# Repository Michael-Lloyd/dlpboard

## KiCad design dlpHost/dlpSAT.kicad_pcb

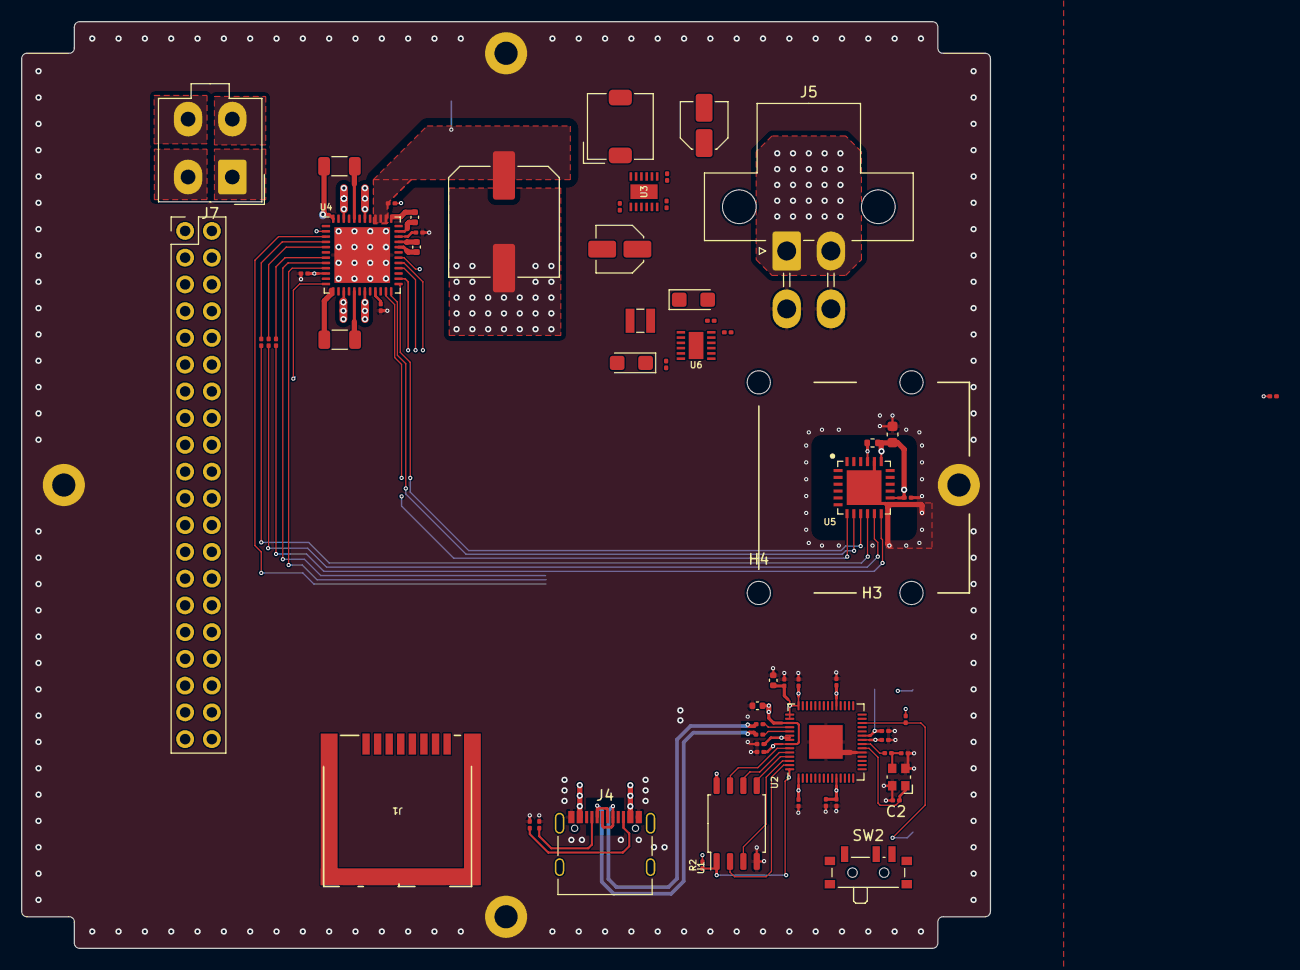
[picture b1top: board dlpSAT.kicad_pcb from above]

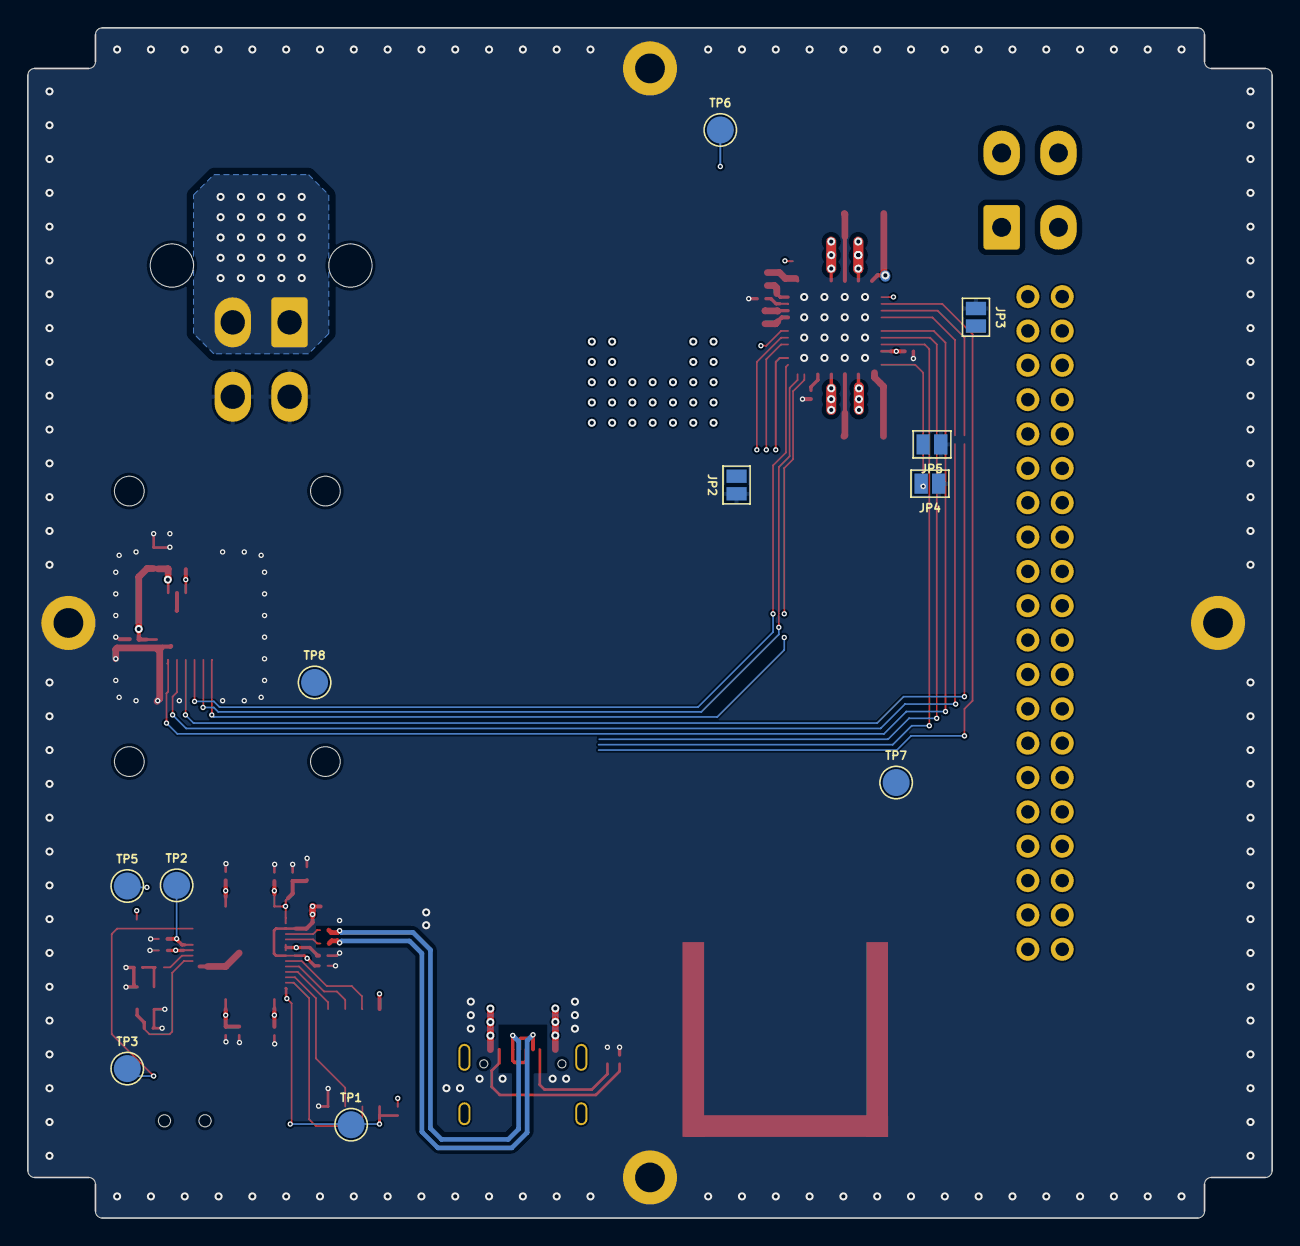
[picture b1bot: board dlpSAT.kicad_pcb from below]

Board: 4 copper layers, 92.0 x 88.0 mm, 77 parts (11 on the bottom side), 49 nets.

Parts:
BRD1: 100STD_BLUESAT; Rocket_Layout
C2, C3: C; C_0201_0603Metric
C4, C15: 1µF; C_0402_1005Metric
C5, C6, C7, C8, C9, C10, C11, C12, C13, C14, C17, C18, C19, C22, C25, C26, C27, C28, C33, C34, C35: 100nF; C_0201_0603Metric
C16: 10µF; C_0603_1608Metric
C20: 100µF; C_Elec_10x10.2
C21: 22nF, 63V; C_0402_1005Metric
C23: 470nF; C_0201_0603Metric
C24: 4.7µF; C_0402_1005Metric
C29, C30: 100µF; C_Elec_4x5.4
C31, C32: C_Polarized_US; CP_EIA-3216-12_Kemet-S
H2: ENCH1; MountingHole_2.2mm_M2
H3: ENCH2; MountingHole_2.2mm_M2
H4: ENCH3; MountingHole_2.2mm_M2
H5: ENCH4; MountingHole_2.2mm_M2
J1: DM3CS-SF
J4: USB_C_Receptacle_USB2.0; USB_C_Receptacle_Palconn_UTC16-G
J5: Power Input; Molex_Mini-Fit_Jr_5569-04A1
J7: Stepper Motor Connector; Molex_Mini-Fit-5566
JP2: DRV_EN; SolderJumper-2_P1.3mm_Open_Pad1.0x1.5mm
JP3: TEST; SolderJumper-2_P1.3mm_Open_Pad1.0x1.5mm
JP4: SPI_MODE; SolderJumper-2_P1.3mm_Open_Pad1.0x1.5mm
JP5: SS_MODE; SolderJumper-2_P1.3mm_Open_Pad1.0x1.5mm
L1: L; L_Wuerth_MAPI-2512
L2: L; L_TDK_SLF6025
R1, R17, R18: R; R_0201_0603Metric
R2: 10kΩ; R_0201_0603Metric
R3, R4: 27Ω; R_0201_0603Metric
R5: 1kΩ; R_0201_0603Metric
R6: 1kΩ; R_0402_1005Metric
R8, R9: R; R_1206_3216Metric
R10, R11, R12: 0Ω; R_0201_0603Metric
SW2: SW_DPST; SW_SPDT_PCM12
TP1, TP2, TP3, TP5, TP6, TP7, TP8: TestPoint; TestPoint_Pad_D2.0mm
U1: W25Q128JVS; SOIC-8_5.23x5.23mm_P1.27mm
U2: RP2040; QFN-56-1EP_7x7mm_P0.4mm_EP3.2x3.2mm
U3, U6: LMR51450SDRRR
U4: TMC5130A-TA-T; QFN-48-1EP_7x7mm_P0.5mm_EP5.3x5.3mm
U5: AEAT-8800-Q24
Y1: 12MHz; Crystal_SMD_Abracon_ABM10-4Pin_2.5x2.0mm

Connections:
+1V1: C4.1, C5.1, C6.1, TP2.1, U2.23 (DVDD), U2.45 (VREG_VOUT), U2.50 (DVDD)
+3.3V: C7.1, C8.1, C9.1, C10.1, C11.1, C12.1, C13.1, C14.1, C15.1, C16.1, C17.1, C25.1, R1.1, R2.1, R6.1, TP5.1, U1.8 (VCC), U2.1 (IOVDD), U2.10 (IOVDD), U2.22 (IOVDD), U2.33 (IOVDD), U2.42 (IOVDD), U2.43 (ADC_AVDD), U2.44 (VREG_IN), U2.48 (USB_VDD), U2.49 (IOVDD), U4.10 (VCC_IO), U5.14 (VDDA), U5.19 (VDDA)
+5V: C23.2, U4.34 (VCC)
+12V: J5.1, J5.2
/Connectors/CC1: J4.A5 (CC1), R18.1
/Connectors/CC2: J4.B5 (CC2), R17.1
/RP2040/QSPI_CLK: U1.6 (CLK), U2.52 (QSPI_SCLK)
/RP2040/QSPI_D0: U1.5 (DI(IO0)), U2.53 (QSPI_SD0)
/RP2040/QSPI_D1: U1.2 (DO(IO1)), U2.55 (QSPI_SD1)
/RP2040/QSPI_D2: U1.3 (IO2), U2.54 (QSPI_SD2)
/RP2040/QSPI_D3: U1.7 (IO3), U2.51 (QSPI_SD3)
/RP2040/QSPI_~CS: R2.2, TP1.1, U1.1 (~CS), U2.56 (QSPI_SS)
ENC_A: TP8.1, U4.25 (ENCA), U5.9 (DATA_A)
ENC_B: U4.24 (ENCB), U5.8 (DATA_B)
GND: BRD1.M1, BRD1.M2, BRD1.M3, BRD1.M4, C2.2, C3.2, C4.2, C5.2, C6.2, C7.2, C8.2, C9.2, C10.2, C11.2, C12.2, C13.2, C14.2, C15.2, C16.2, C17.2, C22.2, C23.1, C25.2, J4.A1 (GND), J4.A12 (GND), J4.B1 (GND), J4.B12 (GND), J5.3, J5.4, JP2.1 (A), JP3.1 (A), JP4.1 (A), JP5.1 (A), R17.2, R18.2, U1.4 (GND), U2.19 (TESTEN), U2.57 (GND), U4.49 (PAD), U5.13 (GND), U5.20 (GND), U5.25 (GND), Y1.2, Y1.4
GNDA: C24.1, U4.32 (GNDA)
GNDPWR: C18.2, C19.2, C20.2, R8.2, R9.2, U4.13 (GNDP), U4.48 (GNDP)
unnamed: C3.1, R5.1, Y1.3
unnamed: J1.10 (GND), J1.11 (GND), J1.12 (GND), J1.13 (GND)
unnamed: JP2.2 (B), U4.29 (DRV_ENN)
unnamed: JP3.2 (B), U4.1 (TST_MODE)
unnamed: JP4.2 (B), U4.12 (SPI_MODE)
unnamed: JP5.2 (B), U4.11 (SD_MODE)
unnamed: R1.2, TP3.1, U2.26 (RUN)
unnamed: R4.2, U2.46 (USB_DM)
unnamed: R3.2, U2.47 (USB_DP)
unnamed: C2.1, U2.20 (XIN), Y1.1
unnamed: R5.2, U2.21 (XOUT)
unnamed: R12.1, U4.7 (MISO)
unnamed: R11.1, U4.5 (MOSI)
unnamed: R10.1, U4.4 (SCK)
unnamed: C24.2, U4.33 (5VOUT)
unnamed: C21.2, U4.37 (CPI)
unnamed: C21.1, U4.35 (CPO)
unnamed: R8.1, U4.44 (BRA)
unnamed: R9.1, U4.17 (BRB)
SPI0_MISO: R11.2, U5.11 (SPI_MOSI)
SPI0_MOSI: R12.2, U5.12 (SPI_MISO)
SPI0_SCK: R10.2, U5.10 (SPI_SCK)
SPI0_~CS_DRIVER: TP7.1, U4.3 (~CS)
SPI0_~CS_ENC: R6.2, U5.21 (SPI_~CS)
STEPPER_A1: J7.1, U4.46 (OA1)
STEPPER_A2: J7.3, U4.42 (OA2)
STEPPER_B1: J7.2, U4.15 (OB1)
STEPPER_B2: J7.4, U4.19 (OB2)
USB_D+: J4.A7 (D-), J4.B7 (D-), R3.1
USB_D-: J4.A6 (D+), J4.B6 (D+), R4.1
VBUS: J4.A4 (VBUS), J4.A9 (VBUS), J4.B4 (VBUS), J4.B9 (VBUS)
VPP: C18.1, C19.1, C20.1, C22.1, TP6.1, U4.21 (VS), U4.38 (VCP), U4.39 (VSA), U4.40 (VS)
